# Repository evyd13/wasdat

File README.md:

# Wasdat and Wasdat Code
The Wasdat and Wasdat Code are are replacement controllers for the WASD V2 and WASD CODE V2B, respectively.

# Use KiCAD nightly!
If you have any trouble opening these files, please download and install the lastest nightly build of KiCAD.

# Read the license!
As with all my projects, please read the license before using these files.

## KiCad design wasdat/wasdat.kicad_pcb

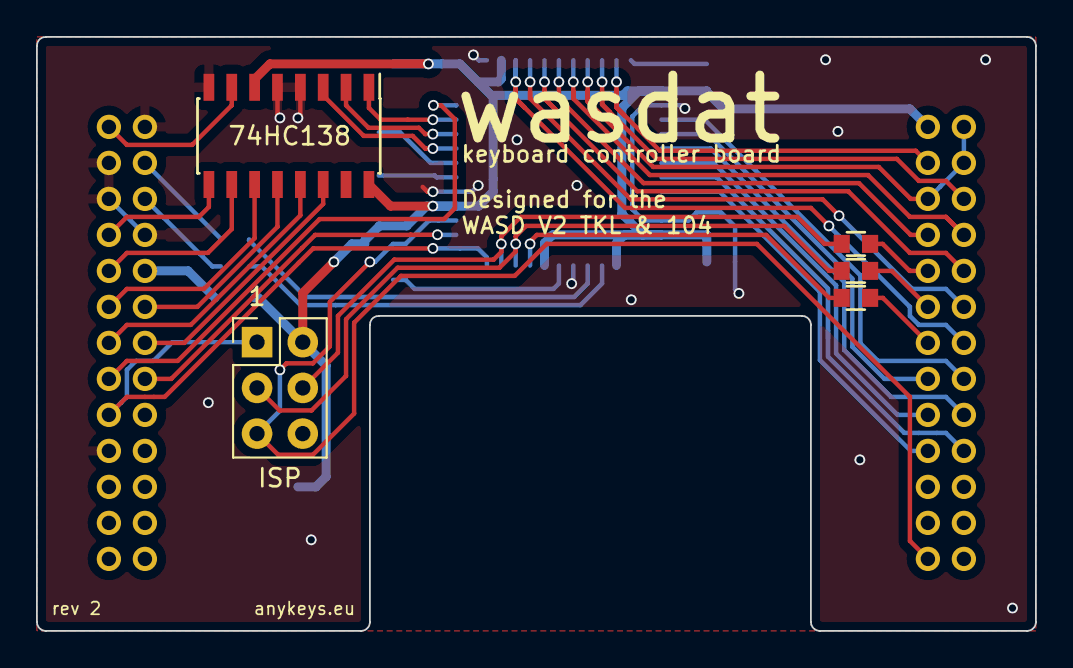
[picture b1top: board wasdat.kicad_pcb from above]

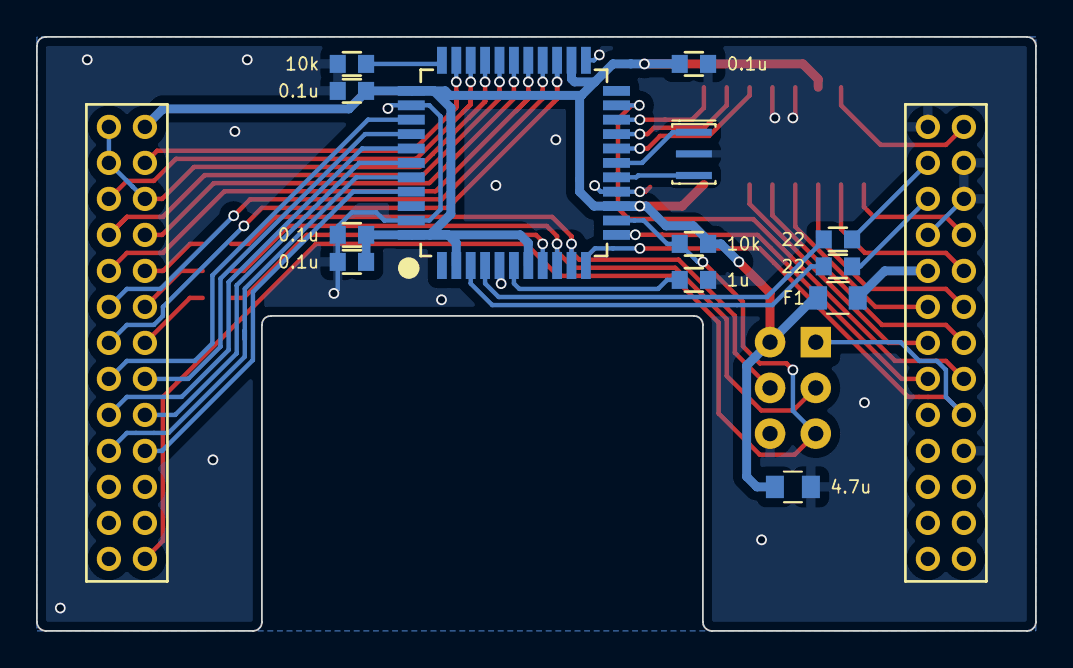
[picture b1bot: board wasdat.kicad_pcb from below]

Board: 2 copper layers, 55.5 x 33.0 mm, 20 parts (13 on the bottom side), 45 nets.

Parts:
C1, C2, C3, C4: 0.1u; C_0603
C5: 4.7u; C_0805
C6: 1u; C_0603
F1: Polyfuse_Small; R_0805
H1: Left; PinHeader_2x13_P2.00mm_Vertical
H2: Right; PinHeader_2x13_P2.00mm_Vertical
J1: ISP; isp_standard
R1, R2: 22; R_0603
R3, R4: 10k; R_0603
R5, R6, R7: 1k; R_0603
U1: ATmega32U4; ATMEGA32U4
U2: 74HC138; SOIC-16_3.9x9.9mm_P1.27mm
X1: 16mhz; Resonator_SMD_muRata_CSTNExxV-3Pin-p1.2

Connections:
A0: U1.20 ((RXD/INT2)PD2), U2.1 (A0)
A1: U1.19 ((SDA/INT1)PD1), U2.2 (A1)
A2: U1.18 ((OC0B/SCL/INT0)PD0), U2.3 (A2)
D+: H1.4, R1.2
D-: H1.6, R2.2
DIP_1: H2.25, J1.5, R3.2, U1.13 (RESET)
GND: C1.2, C2.2, C3.2, C4.2, C5.2, C6.2, H1.2, H1.3, H1.5, H1.8, H1.19, J1.6, R4.2, U1.5 (UGND), U1.15 (GND), U1.23 (GND), U1.35 (GND), U1.43 (GND), U2.4 (~GL), U2.5 (~G2), U2.8 (GND), X1.3
LED_caps: R7.2, U1.8 ((SS/PCINT0)PB0)
LED_num: J1.4, R5.2, U1.10 ((PDI/MOSI/PCINT2)PB2)
LED_scroll: J1.3, R6.2, U1.9 ((SCLK/PCINT1)PB1)
MISO: H1.17, J1.1, U1.11 ((PDO/MISO/PCINT3)PB3)
unnamed: C6.1, U1.6 (UCAP)
unnamed: F1.2, H1.10
unnamed: H2.9, R5.1
unnamed: H2.11, R6.1
unnamed: H2.13, R7.1
unnamed: R1.1, U1.4 (D+)
unnamed: R2.1, U1.3 (D-)
unnamed: R4.1, U1.33 ((~HWB~)PE2)
unnamed: U1.16 (XTAL2), X1.2
unnamed: U1.17 (XTAL1), X1.1
VCC: C1.1, C2.1, C3.1, C4.1, C5.1, F1.1, H2.1, J1.2, R3.1, U1.2 (UVCC), U1.7 (VBUS), U1.14 (VCC), U1.24 (AVCC), U1.34 (VCC), U1.44 (AVCC), U2.6 (G1), U2.16 (VCC)
col0: H2.3, U1.32 ((ICP3/CLK0/OC4A)PC7)
col1: H2.2, H2.4, H2.5, U1.30 ((ADC13/OC1B/OC4B/PCINT13)PB6)
col2: H2.6, U1.31 ((OC3A/~OC4A~)PC6)
col3: H2.7, U1.28 ((ADC11/PCINT4)PB4)
col4: H2.8, U1.29 ((ADC12/OC1A/~OC4B~/PCINT12)PB5)
col5: H2.10, U1.27 ((T0/OC4D/ADC10)PD7)
col6: H1.1, U2.7 (Y7)
col7: H1.7, U2.9 (Y6)
col8: H1.9, U2.10 (Y5)
col9: H1.11, U2.11 (Y4)
col10: H1.12, U2.12 (Y3)
col11: H1.13, U2.13 (Y2)
col12: H1.14, U2.14 (Y1)
col13: H1.15, U1.21 ((TXD/INT3)PD3)
col14: H1.16, U1.12 ((OC0A/OC1C/~RTS~/PCINT7)PB7)
row0: H2.12, U1.26 ((T1/~OC4D~/ADC9)PD6)
row1: H2.14, U1.25 ((ICP2/ADC8)PD4)
row2: H2.15, U1.37 ((ADC6/TDO)PF6)
row3: H2.16, U1.36 ((ADC7/TDI)PF7)
row4: H2.17, U1.39 ((ADC4/TCK)PF4)
row5: H2.18, U1.38 ((ADC5/TMS)PF5)
row6: H2.19, U1.41 ((ADC0)PF0)
row7: H2.20, U1.40 ((ADC1)PF1)

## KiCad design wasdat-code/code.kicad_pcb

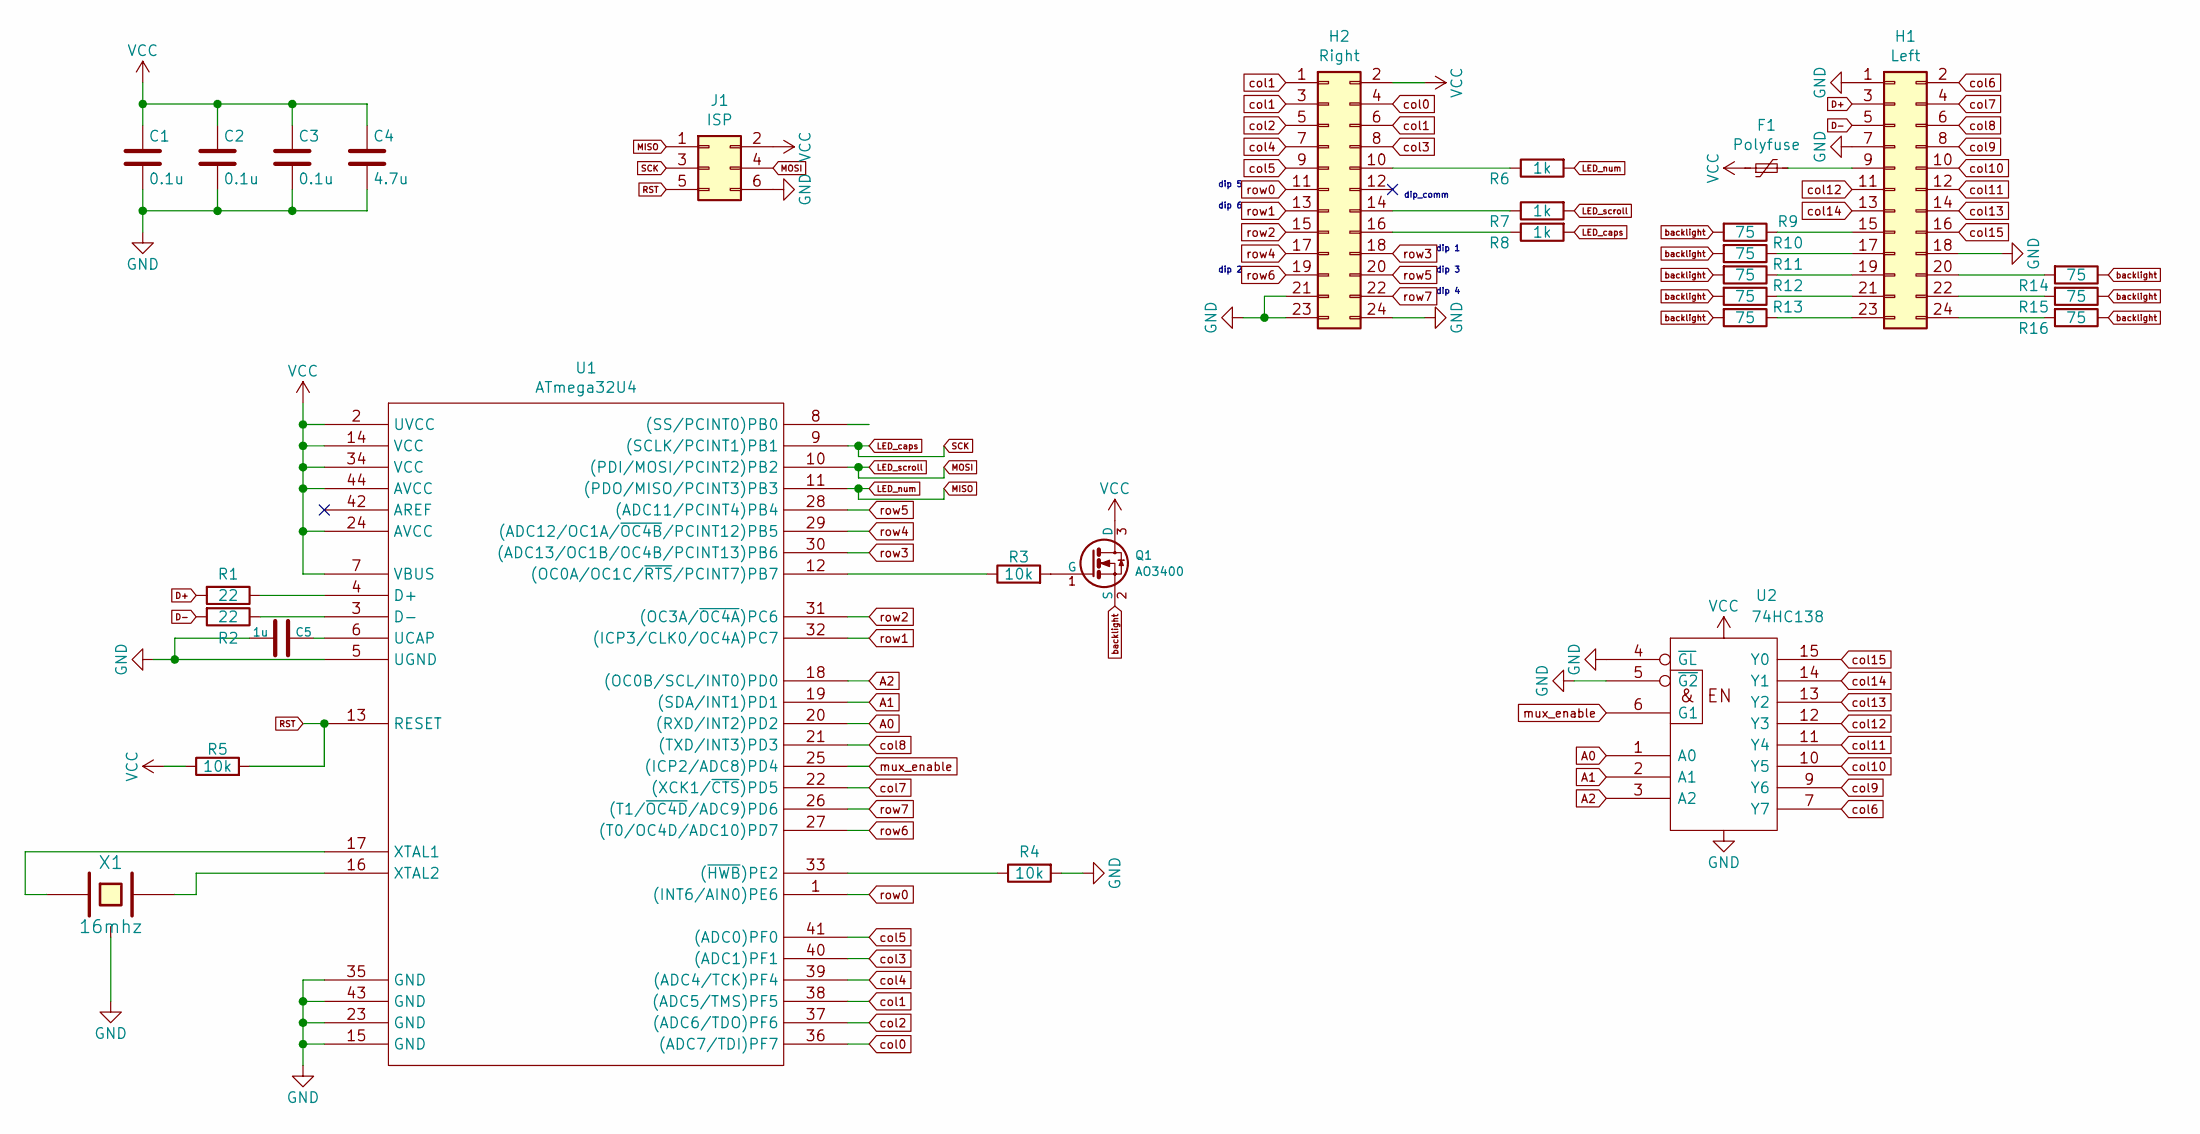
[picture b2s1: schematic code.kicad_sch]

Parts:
C1, C2, C3: 0.1u; C_0603
C4: 4.7u; C_0805
C5: 1u; C_0603
F1: Polyfuse; R_0805
H1: Left; PinHeader_2x12_P2.00mm_Vertical
H2: Right; PinHeader_2x12_P2.00mm_Vertical
J1: ISP; isp_standard
Q1: AO3400; SOT-23
R1, R2: 22; R_0603
R3, R4, R5: 10k; R_0603
R6, R7, R8: 1k; R_0603
R9, R10, R11, R12, R13, R14, R15, R16: 75; R_0805
U1: ATmega32U4; ATMEGA32U4
U2: 74HC138; SOIC-16_3.9x9.9mm_P1.27mm
X1: 16mhz; Resonator_SMD_muRata_CSTNExxV-3Pin-p1.2

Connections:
A0: U1.20 ((RXD/INT2)PD2), U2.1 (A0)
A1: U1.19 ((SDA/INT1)PD1), U2.2 (A1)
A2: U1.18 ((OC0B/SCL/INT0)PD0), U2.3 (A2)
D+: H1.3, R1.2
D-: H1.5, R2.2
GND: C1.2, C2.2, C3.2, C4.2, C5.2, H1.1, H1.7, H1.18, H2.21, H2.23, H2.24, J1.6, R4.2, U1.5 (UGND), U1.15 (GND), U1.23 (GND), U1.35 (GND), U1.43 (GND), U2.4 (~GL), U2.5 (~G2), U2.8 (GND), X1.3
LED_caps: J1.3, R8.2, U1.9 ((SCLK/PCINT1)PB1)
LED_num: J1.1, R6.2, U1.11 ((PDO/MISO/PCINT3)PB3)
LED_scroll: J1.4, R7.2, U1.10 ((PDI/MOSI/PCINT2)PB2)
unnamed: F1.2, H1.9
unnamed: H1.15, R9.1
unnamed: H1.17, R10.1
unnamed: H1.19, R11.1
unnamed: H1.20, R14.2
unnamed: H1.21, R12.1
unnamed: H1.22, R15.2
unnamed: H1.23, R13.1
unnamed: H1.24, R16.2
unnamed: H2.10, R6.1
unnamed: H2.14, R7.1
unnamed: H2.16, R8.1
unnamed: Q1.1 (G), R3.2
unnamed: R2.1, U1.3 (D-)
unnamed: R3.1, U1.12 ((OC0A/OC1C/~RTS~/PCINT7)PB7)
unnamed: R4.1, U1.33 ((~HWB~)PE2)
unnamed: U1.16 (XTAL2), X1.2
unnamed: U1.17 (XTAL1), X1.1
RST: J1.5, R5.2, U1.13 (RESET)
VCC: C1.1, C2.1, C3.1, C4.1, F1.1, H2.2, J1.2, Q1.3 (D), R5.1, U1.2 (UVCC), U1.7 (VBUS), U1.14 (VCC), U1.24 (AVCC), U1.34 (VCC), U1.44 (AVCC), U2.16 (VCC)
backlight: Q1.2 (S), R9.2, R10.2, R11.2, R12.2, R13.2, R14.1, R15.1, R16.1
col0: H2.4, U1.36 ((ADC7/TDI)PF7)
col1: H2.1, H2.3, H2.6, U1.38 ((ADC5/TMS)PF5)
col2: H2.5, U1.37 ((ADC6/TDO)PF6)
col3: H2.8, U1.40 ((ADC1)PF1)
col4: H2.7, U1.39 ((ADC4/TCK)PF4)
col5: H2.9, U1.41 ((ADC0)PF0)
col6: H1.2, U2.7 (Y7)
col7: H1.4, U1.22 ((XCK1/~CTS~)PD5)
col8: H1.6, U1.21 ((TXD/INT3)PD3)
col9: H1.8, U2.9 (Y6)
col10: H1.10, U2.10 (Y5)
col11: H1.12, U2.11 (Y4)
col12: H1.11, U2.12 (Y3)
col13: H1.14, U2.13 (Y2)
col14: H1.13, U2.14 (Y1)
col15: H1.16, U2.15 (Y0)
mux_enable: U1.25 ((ICP2/ADC8)PD4), U2.6 (G1)
row0: H2.11, U1.1 ((INT6/AIN0)PE6)
row1: H2.13, U1.32 ((ICP3/CLK0/OC4A)PC7)
row2: H2.15, U1.31 ((OC3A/~OC4A~)PC6)
row3: H2.18, U1.30 ((ADC13/OC1B/OC4B/PCINT13)PB6)
row4: H2.17, U1.29 ((ADC12/OC1A/~OC4B~/PCINT12)PB5)
row5: H2.20, U1.28 ((ADC11/PCINT4)PB4)
row6: H2.19, U1.27 ((T0/OC4D/ADC10)PD7)
row7: H2.22, U1.26 ((T1/~OC4D~/ADC9)PD6)

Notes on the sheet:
dip 5
dip 6
dip 2
dip_comm
dip 1
dip 3
dip 4

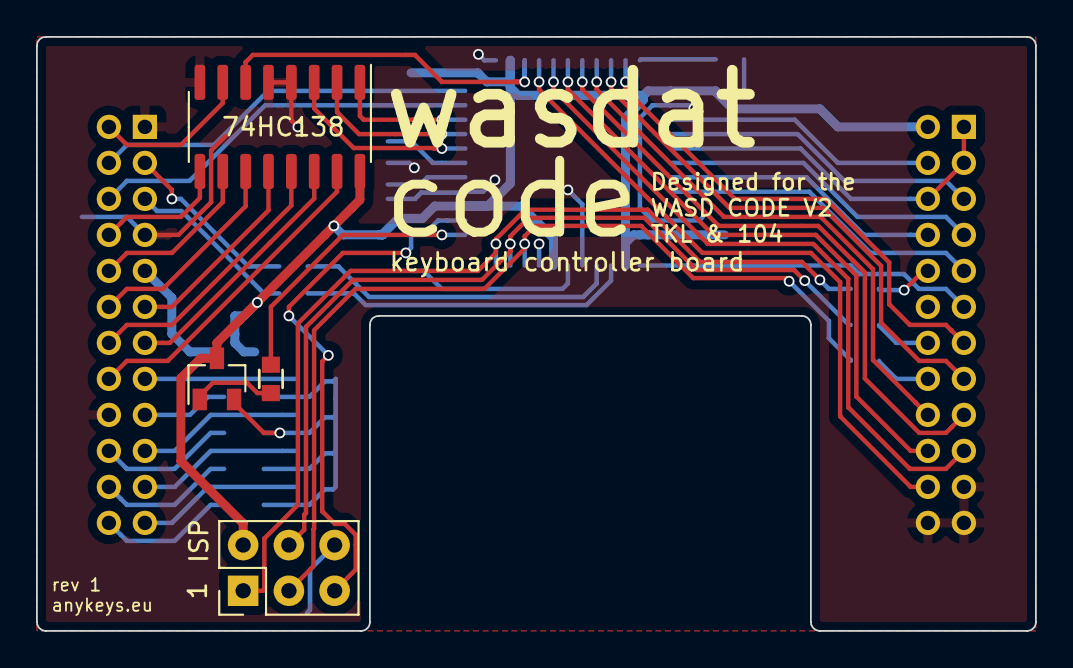
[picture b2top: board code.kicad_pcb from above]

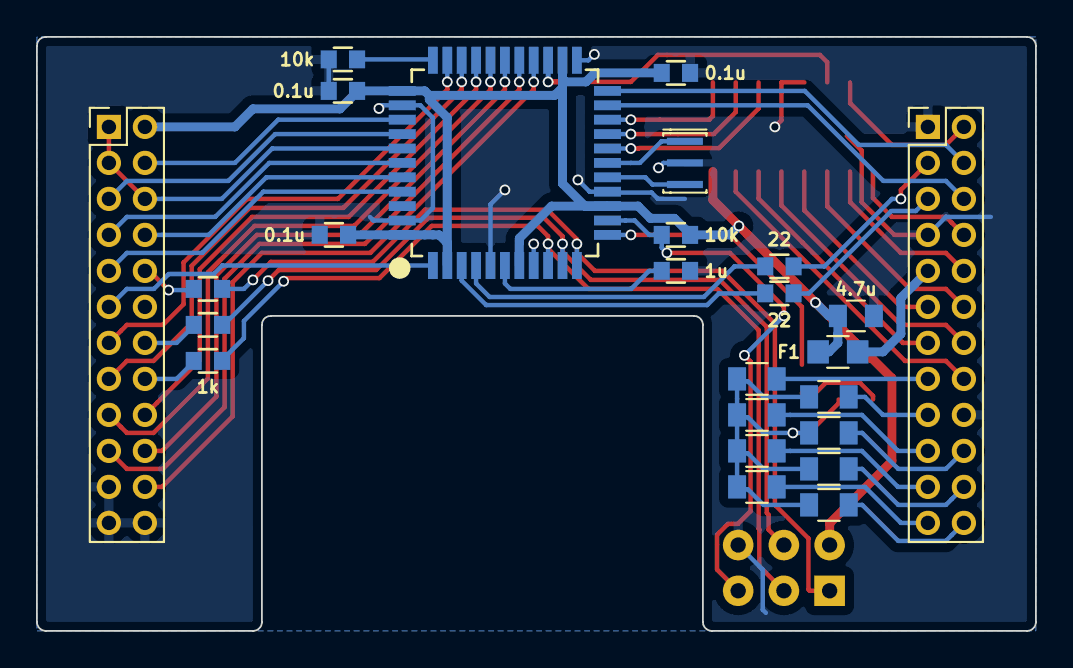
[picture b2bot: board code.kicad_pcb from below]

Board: 2 copper layers, 55.5 x 33.0 mm, 29 parts (25 on the bottom side), 55 nets.

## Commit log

2021-04-27 Upload files
2021-06-14 C
    Change amount of caps and fix wrong mcu package
